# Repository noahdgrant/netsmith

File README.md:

<h1 align="center">
  <picture>
    <source media="(prefers-color-scheme: dark)" srcset="docs/assets/logo-dark.svg">
    
  </picture>
</h1>

A language and tools for designing electronics as code: schematics, solvers, checks and PCB fabrication outputs.
A board is a set of parts and the nets that join their pins,
written as text. netsmith checks it, picks real parts that work in the worst case, and
exports files for CAD tools and for a board house. It writes a KiCad 9 schematic, and a placed
and routed PCB with a Gerber package for JLCPCB, on two layers or on four with ground and
supply planes inside. The editor (`netsmith view editor`) shows the source and the board in a
browser.

Status: early (v0.1). The examples in `examples/` build and pass KiCad's checks where KiCad is installed, except `carrier_and_cards.nsm`, whose invented parts have no KiCad symbol (it is checked and solved only). The rest build and fab with no KiCad at all (see Install). Some of the decisions behind the language are still `proposed` and wait for review (see Limitations).

## An example

`examples/led.nsm` is a board with a 5 V supply, a resistor and an LED. The `~>` line is the
series circuit, and it carries its own equation: the supply's voltage less the LED's forward
voltage, over the resistance, is the LED's current. netsmith picks a resistor and an LED from a
catalog so that the current stays in the LED's window in the worst case, for every tolerance.

```nsm
board LedExample {
    .process: TwoLayer {
        .stackup.thickness &= 1.6mm
    }

    .supply: Rail {
        .voltage &= 5V +/- 5%
        .pos.net &= "VCC"
    }
    .led: Led {
        .current &= 5mA..15mA
    }
    .r1: Resistor {}

    .power_in: Header1x2
    .supply.pos ~ .power_in.p1
    .supply.neg ~ .power_in.p2

    .supply.pos ~> .r1 ~> .led ~> .supply.neg
}
```

The imports and doc comments are left out here; the complete file is `examples/led.nsm`.

## Install

- Build from a checkout: `cargo install --path crates/netsmith-cli --locked` (the package is
  `netsmith-cli`; the program it installs is `netsmith`). It needs Rust; with Node 20 or newer
  it also builds the editor's page (without Node the editor shows a page that says it was not
  built, ADR 0114).
- Or straight from GitHub, with no checkout:
  `cargo install --git https://github.com/noahdgrant/netsmith netsmith-cli --locked`.
- Or take the `netsmith-<version>-<target>.tar.gz` archive (`.zip` on Windows) from the
  [releases](https://github.com/noahdgrant/netsmith/releases), check it against its `.sha256`
  file and put the binary on your `PATH`. The release workflow builds them for Linux, macOS and
  Windows (`scripts/release-build.sh` makes one) and attaches them to a release when its tag is
  pushed. v0.1.0 and v0.3.0 have none (their builds failed; 0.3.1 is the first of the 0.3 line
  with archives): the release pull request now runs the same build before it is merged.
- netsmith is not on crates.io yet.

### KiCad is optional

netsmith needs no KiCad to write, check, solve, see, build or fab a board, and it needs no
KiCad library or `kicad-cli` for any of them (ADR 0097). It draws the ICs and the linear
regulator from the part's pin table, as a plain box, and the resistors, capacitors, inductors,
LEDs, diodes, FETs, fuses, crystals, switches, ferrite beads, headers and sockets, USB-C and
coaxial connectors, test points, mounting holes, fiducials and the power flag as conventional
glyphs, with the pins where KiCad's symbols have them. Every footprint of the standard
library is generated or written from the maker's drawing (`std/libs/`). The `.kicad_sch` and
`.kicad_pcb` files it writes are KiCad's formats, and KiCad opens them. CI proves it: the
`no-kicad` job builds and fabs the examples on a runner with no KiCad, with the libraries and
`kicad-cli` hidden (`scripts/check-no-kicad.sh`), and fails if a run says KiCad is missing. No
example names a part of KiCad's own, so every one of them builds and fabs.

KiCad 9 is needed for these, and for nothing else:

- The ERC and DRC cross-check: `kicad-cli`, and in the editor the PCB findings that run
  KiCad's check (without it the findings list says "KiCad not found: set KICAD_CLI or install
  KiCad", once). `board fab --cross-check` plots the board with KiCad as well (with no KiCad it compares the
  Gerbers with the board with netsmith's own viewer alone), and `fab` runs netsmith's own design
  rules check without it.
- A project whose own `kicad.toml` names a KiCad symbol or footprint that netsmith does not
  make, with no `[[library]]` of the project and no `gen:` footprint for it. Only then does a
  run stop, and the message names the part, the id and the line of `kicad.toml`, lists where
  netsmith looked, and gives the three ways out: install KiCad 9, supply the file through a
  `[[library]]`, or use a `gen:` footprint (or omit `symbol`, to have the symbol drawn from the
  pin table).

netsmith finds KiCad's `symbols` and `footprints` folders by itself, and `kicad-cli` as
`$KICAD_CLI`, else `kicad-cli` or `kicad-cli.exe` on `PATH`, else (under WSL only) the newest Windows KiCad in
`/mnt/c/Program Files/KiCad/<version>/bin`; set `NETSMITH_KICAD_SYMBOLS` and
`NETSMITH_KICAD_FOOTPRINTS` to name the folders. `NETSMITH_NO_KICAD=1` makes every one of those
searches find nothing, whatever is installed (for tests and CI). KiCad 9 is the version
tested: Windows KiCad 9 under WSL on a real install, KiCad 9 on Linux in the CI `kicad` job,
and, in the release workflow, the starter board's `init`, `build` and `fab` with KiCad 10 on
macOS and Windows runners (#6). The folders of KiCad 8 are looked for too, and nobody has
tried them.

## Use it

```sh
mkdir blink && cd blink
netsmith project init       # netsmith.toml, src/main.nsm (a working LED board), agent files (`project refresh` updates them after an upgrade)
netsmith board build      # a KiCad schematic in out/
netsmith view editor     # the source and the board in a browser, at 127.0.0.1:8787 (`--offline` asks no supplier for stock or price, and the bill of materials says they are not checked; `board fab --offline` says it in `fab-notes.txt`)
netsmith board fab        # a package for JLCPCB in fab/: Gerbers, drill, bom.csv, cpl.csv, fab-notes.txt, the board's 3D scene as `<board>.glb` (`--no-glb` or `glb = false` in netsmith.toml leaves it out), the board as STEP for mechanical CAD as `<board>.step` (`--no-step` or `step = false` leaves it out), the schematic as `<board>-schematic.pdf`, a page for each sheet (`--no-pdf` or `pdf = false` leaves it out), and for a board with pin requests its pin map for firmware from the final layout (`.pins.h`, `.pins.json`)
netsmith dev board3d --format json   # the board's 3D facts for an agent: heights, limits, overlaps (docs/BOARD3D.md)
netsmith dev board3d --glb board.glb   # the same scene as glTF 2.0 binary, the file the editor's 3D view shows
netsmith view 3d --view iso --picture board.png   # the board drawn in 3D to a PNG by netsmith's own rasterizer, no GPU or KiCad (docs/BOARD3D.md)
netsmith view schematic --format pdf   # the schematic the editor draws as a PDF, a page for each sheet (`--format svg` or `png` for a picture, `--sheet NAME` for one sheet), no KiCad or browser
netsmith view editor-3d --view top --highlight J1 --picture j1.png   # drive the 3D view of the running editor with render's flags, and save its picture (docs/BOARD3D.md)
netsmith layout show   # where each part is in the layout file; `layout set PATH --at X,Y --turn 90 --side bottom --lock` writes one entry, `layout check` finds a wrong path or turn, `layout summary` sums up a placement (wire, decoupling, modules, area and free space per face, nets, the parts near a part, the distance between two pads; the editor's PCB view has it as the Summary tab) `layout compare` says what moved between two layout files, `layout regenerate PATH` places one module again with the rest held, `layout capture` writes the placement and its seed as the layout file, an entry for every part, to freeze a result, `layout fit PATH` says where one part fits with the rest where they are (`--as-laid-out` asks of the layout file's board with nothing placed), `layout parts [PATH...]` gives each part's frame, courtyard shapes and pads (net, place, size) as data, with the placement's findings beside them, and `layout export --out FILE.kicad_pcb` writes the placed board, not routed, for KiCad (also with findings), whose moved parts `layout import FILE.kicad_pcb` brings back (the editor's PCB view has the same files as its "Download KiCad board" button; language guide, "The layout file")
netsmith board compare a.kicad_sch b.nsm   # are two designs the same circuit?
netsmith mcp   # the commands as tools for an agent host over the Model Context Protocol; `claude mcp add netsmith -- netsmith mcp`, `--project DIR` for a host that cannot start it in the project's folder, `--editor [PORT]` to act on the page of a running editor; a short tool list, the whole help of a command a resource (language guide, "The MCP server")
netsmith board compare --ref main          # what changed in the circuit since the branch `main`
```

Without a project, `netsmith board build examples/led.nsm --out out` works on one file. `netsmith
--help` and `netsmith <command> --help` document every command and flag, and `docs/LANGUAGE.md` ("Projects and netsmith.toml")
describes the project folder.

The first `build` or `fab` also writes `src/main.lock.toml` beside each source file: the catalog
row each part was picked as. Commit it, as you commit `Cargo.lock`. Later runs hold each part
to its row, and `--locked` makes a run that would change the picks an error (`docs/LANGUAGE.md`,
"The pick lock"). `netsmith project lock --update` refreshes the lock after a catalog edit and prints
what changed (`--part r1,u2` or `--except r1` takes new picks for some parts only), and
`netsmith project lock --check` fails when it is not current, for CI. `lock = "top_level"` or `"none"` under
`[project]` in `netsmith.toml` keeps unit-test and scratch sources free of lock files.

The boards in `examples/` carry their locks, committed beside the sources, and CI runs
`netsmith project lock --check` over every one of them (`scripts/check-example-locks.sh`, the `locks` job). A
change to a catalog, `std/` or the solver that would move a pick of an example fails the job until
someone runs `netsmith project lock --update` in the example and the diff of the lock is reviewed. Each
example also commits its design, `<stem>.design.json` (`netsmith board build --emit-design`), which the
`designs` job checks the same way (`scripts/check-example-designs.sh`, whose `--update` rewrites it).
`NETSMITH_TIMINGS=1` prints how long each stage took.

The editor also opens in a window of its own: the desktop shell in `desktop/` (a separate Cargo
workspace, built with Tauri, on Linux for now) starts `netsmith view editor` in the project folder it is
opened with (`netsmith-desktop [FOLDER]`, the current folder by default) on a free port, shows it,
and stops it when the window closes. It needs WebKitGTK (`libwebkit2gtk-4.1-dev`) to build:
`cargo build --manifest-path desktop/Cargo.toml --features window`. It starts the `netsmith` that
`NETSMITH_BIN` names, else the one beside it, else the one on `PATH`. No release ships it yet.

**Read `fab-notes.txt` before you order.** It lists what netsmith could not verify, for
example the pick-and-place rotation of a package that no board of yours has been assembled
with, the parts you solder yourself (`hand-solder:`), the parts you ship to the board house
(`consigned:`, ADR 0084) and, for each supply channel, the numbers to buy those by (`buy from`,
ADR 0143). Check JLCPCB's order preview for those.

## Where to read next

- `docs/LANGUAGE.md`: the language guide's index; its chapters are in `docs/language/`, with a quick
  start, every construct with a tested example and the real error you get when you misuse it, and the
  standard library.
- `docs/PIPELINE.md`: the stages a design goes through, from source to a fab package, with diagrams.
- `docs/BOARD3D.md`: `netsmith dev board3d`, the board's 3D scene as a JSON report and as a `.glb` file, and `netsmith view 3d`, the same scene as a PNG, and `netsmith view editor-3d`, which drives the 3D view of a running editor.
- `docs/CONCEPTS.md`: how parts, modules, boards and systems combine.
  `docs/PROJECT-LAYOUT.md`: a repository with several boards.
- `docs/MIGRATING.md`: what to change in a project that a newer netsmith refuses, release by release, with the old and the new spelling.
- `docs/RELEASING.md`: the order of a release, with the `kicad-cli` stress run (`scripts/stress-kicad.sh`).
- `docs/symbol-gallery.html` (open it in a browser): every symbol netsmith draws, beside the KiCad
  symbol it replaces. `cargo run -p netsmith-tools --example symbol_gallery -- --out docs --file
  symbol-gallery.html` writes it again.
- `GLOSSARY.md`: the vocabulary (an index of `docs/glossary/`). `docs/DESIGN-RULES.md`: the rules the language follows.
  `docs/adr/`: the decisions behind the design.
- Contributors and agents: `AGENTS.md`. Open work is in the
  [GitHub issues](https://github.com/noahdgrant/netsmith/issues).

## Limitations

netsmith analyzes a worst-case DC operating point of the picked parts: every voltage, current and power is checked over the ranges the design states (ADR 0076). It does not model time. Startup, inrush, ripple, filter response, AC and heating are not analyzed (a part's power rating is checked; its temperature is not computed). Closed-form checks for some of these, such as an RC time constant or a buck's output ripple, are the next step and are laid out as options in `docs/research/closed-form-checks.md`. Running a circuit simulator on demand is a later option, issue #306.

- Price and stock are unknown until a supply provider is asked, and no provider asks a
  supplier yet (#8, #30). Catalogs hold only verified parts (#66). A generic part (a value
  no catalog row has) exists for resistors, ceramic capacitors, inductors and LEDs; a generic
  capacitor has no bias curve and resolves only to a row that has one (ADR 0047, #31).
- netsmith writes its own Gerbers, drill and placement files, and JLCPCB has not yet taken
  them (#12, #61).
- A board outline is a rectangle with equal rounded corners or a `polygon` of corners, fillets
  and arcs, and a cutout is a rounded rectangle, a slot or a circle (#57). A panel repeats
  one board on a V-cut grid (#62).
- The placer and router can leave a tight board unrouted (#3, #58).
- Physical intent (the outline, cutouts, holes, keepouts and where parts must be) is in a file of
  its own beside a board, `<stem>.physical.nsm`, and the same lines in the board are an error
  (ADR 0048, #52). The board level is built, and the placer and `fab` hold a relation between
  two parts (ADR 0045), and the editor writes the keepouts it draws to that file. A module owns a
  physical file of its own, which it names, and a board's file may only narrow it (#813); a
  physical file for a `system` or a `panel` is not built. The readings are in the ADR's "Built".
- Nine ADRs in `docs/adr/` are `proposed` and wait for review: 0049, 0050, 0051, 0072, 0098, 0099, 0100, 0102 and 0103.

## Licence

netsmith is MIT licensed (`LICENSE`).

netsmith keeps no copy of KiCad's symbols or footprints. The symbol of an IC is drawn by
netsmith from the part's pin table (a plain box and pins, ADR 0097), and those of the passives,
discrete parts, connectors and mechanical parts from the electrical and mechanical conventions
(IEC 60617, IEEE 315), not from KiCad's files. Only for a symbol or footprint that a project's
own `kicad.toml` takes from KiCad and that netsmith does not make does it read the ones
installed with KiCad (CC-BY-SA 4.0 with a design exception) at run time. `board build --portable` and
`board fab --portable` copy the library entries a board uses, and their 3D models, into the board's
folder so that it opens in KiCad anywhere; those copies are KiCad's files under CC-BY-SA 4.0, the
folder says so in `LICENSES.md`, and the design in it stays free of the licence by the
exception. The tests that need no KiCad write small libraries of their own (the dev-only crate `netsmith-testkit`). For a package or a part that KiCad's libraries lack,
`std/libs/` holds a small symbol and footprint library of netsmith's own, written by netsmith
from a manufacturer's package drawing (MIT, like the rest; ADR 0087). The footprints it makes are original code that computes
IPC-7351B land patterns from published package dimensions (ADR 0043); the test that checks
them reads KiCad's footprints and bundles none. The formulas and tables were learned from the
`kicad-footprint-generator` repository (GPL-3.0-or-later; no code was copied) and the package
dimensions of the QFN rows are numbers from its data files and the datasheets they cite.

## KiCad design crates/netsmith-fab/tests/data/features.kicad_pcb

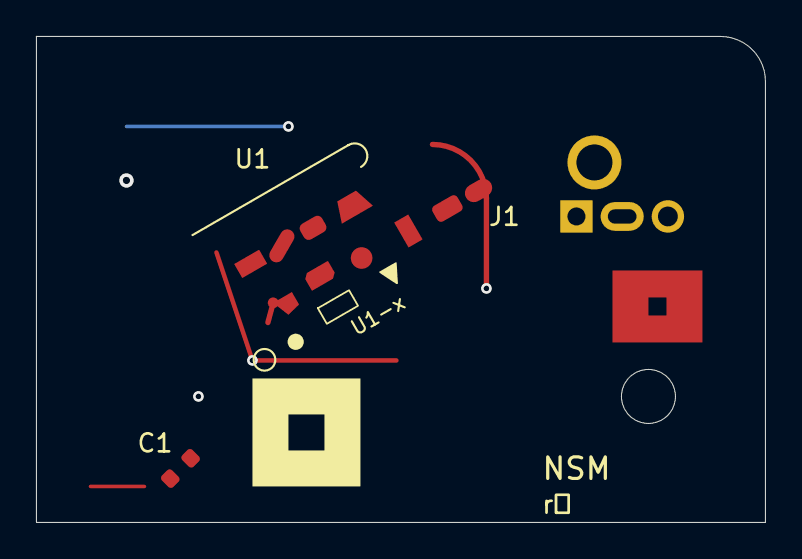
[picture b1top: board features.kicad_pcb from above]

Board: 4 copper layers, 40.5 x 27.0 mm, 4 parts (1 on the bottom side), 3 nets.

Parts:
C1: 100n; C_0603
J1: hdr; Header
R2: 1k; R_0603
U1: shapes; Shapes

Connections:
GND: C1.2, J1.1, R2.1, U1.1, U1.5
SIG: J1.3, R2.2, U1.3, U1.7, U1.8, U1.9, U1.10
VCC: C1.1, J1.2, U1.2, U1.6

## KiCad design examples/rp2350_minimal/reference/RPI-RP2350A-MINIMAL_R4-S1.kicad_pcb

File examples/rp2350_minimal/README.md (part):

# RP2350A Minimal

A port of Raspberry Pi's open **RP2350A Minimal** reference board to netsmith, as a showcase.
**The schematic is done** (`src/main.nsm`, the board `Rp2350Minimal`): the same circuit as
theirs, proved net by net by a test. **The physical file is done** (`src/main.physical.nsm`: the
outline, the four mounting holes, the places of the connectors and buttons), and `netsmith board fab`
writes a PCB that the parity checker finds equal to Raspberry Pi's in every way that must match
(see Parity and The result). Its parts are drawn with Raspberry Pi's footprints (#728, see
Parts), so the placer arranges them otherwise than before, and which seed the router finishes
moved with it: seeds 0 and 4 route completely (about 3 to 4 minutes in a debug build on a busy
machine), seeds 1, 2 and 3 leave three, two and one connection after the router's 300 s (#731).
The design rules check measures the ring of each of the nine vias in the RP2350's exposed pad
with the exposed pad round it, as KiCad does, and finds none too thin (see The reproduction). The
figures of The result are from before.

## Source

- The design: <https://pip.raspberrypi.com/documents/RP-010328-CA>, a zip of the KiCad 10
  schematic, board, project, a PDF and a bill of materials.
- Name and revision: `RPI-RP2350A-MINIMAL_R4-S1`. The board file is revision R4 and the
  schematic is revision S1; both title blocks are dated 2026-07-03 ("RP2350A QFN-60 Minimal
  Design Example"). One schematic sheet, 43 parts, two copper layers.
- Licence: MIT, Copyright (c) 2026 Raspberry Pi Ltd. The notice is in `LICENSE`, as they ship
  it, and stays with every copy of anything in this folder that comes from their design
  (`reference/`).

**The circuit is Raspberry Pi's. The port, the netsmith source and the tools in this folder
are netsmith's** (MIT, like the rest of the repository).

## Goal

1. **The same nets.** The schematic of the port and Raspberry Pi's design are the same
   circuit: the test `every_pad_has_the_same_pads_on_its_net_as_in_raspberry_pis_board` proves
   it by comparing the wiring alone (see "Same nets"). The bare `netsmith board compare` of the two
   files answers `different`, because it pairs parts by footprint name (see "Run it").
2. **A matching PCB where it matters.** A board made by `netsmith board fab` is interchangeable
   with theirs in these ways, and a checker with tolerances will fail when one is off:
   - the board outline and the four mounting holes;
   - the connectors (J1 to J4), the buttons (SW1, SW2) and the pin headers: the same
     positions, rotations and pads, with each header pin carrying the same signal.

   The other parts (MCU, flash, crystal, regulator, inductor, decoupling) may be anywhere,
   and the routing will differ; the checker reports them and does not fail on them.

## What is here

- `netsmith.toml`, `src/main.nsm`, `src/oscillator.nsm`, `src/main.lock.toml`: the project, its
  board and the crystal's module (see The board). The lock is the catalog row each part was
  picked as; commit it, refresh it with `netsmith project lock --update`.
- `catalogs/capacitor.csv`, `catalogs/resistor.csv`: two rows the standard catalogs lack, the
  10 uF 0805 capacitor and the 0 ohm link (see The catalog rows).
- `src/tactile_switch.nsm`, `catalogs/ldo.csv`, `catalogs/inductor.csv`,
  `catalogs/tactile_switch.csv`, `kicad.toml`, `libs/rp2350_original.pretty/`: the regulator U2,
  the inductor L1 and the buttons SW1 and SW2 (see Parts).

- `src/rp2350a.nsm`, `catalogs/rp2350a.csv`, `kicad.toml`: the MCU, U1 (see Parts).
- `src/flash.nsm`, `src/crystal.nsm`, `catalogs/w25q128jv.csv`, `catalogs/abm8_272_t3.csv`,
  `kicad.toml`: the QSPI flash, U3, and the crystal, X1 (see Parts).

- `src/amphenol_10103594.nsm`, `src/jst_sm03b_srss_tb.nsm`, `src/samtec_tsw_118.nsm`,
  `catalogs/micro_usb.csv`, `catalogs/jst_srss.csv`, `catalogs/samtec_tsw_118.csv`,
  `libs/rp2350_original.pretty/`: the
  connectors J1 to J4 (see Parts). The footprints are Raspberry Pi's, files of the project's own library, and
  need no KiCad.
- `LICENSE`: Raspberry Pi's licence text.
- `reference/RPI-RP2350A-MINIMAL_R4-S1.kicad_pcb`: their board file, unchanged (1.6 MB).
- `reference/placements.toml`: the facts the checker needs, read from that file: the outline,
  the mounting holes and, for every footprint, its place, rotation and pads. The header of the
  file says what the origin and axes are, and which entries must match (`must_match = true`).
  Regenerate it with
  `cargo run -p netsmith-tools --example reference_table -- reference/RPI-RP2350A-MINIMAL_R4-S1.kicad_pcb > reference/placements.toml`
  (run from this folder); a test checks that the file is what the program prints.
- `reference/parts.toml`: the parts file of the port, Raspberry Pi's designator of each part by its
  member path (see Parity): all 43, the four mounting holes `hole1` to `hole4` as MH1 to MH4. The
  nets proof and the parity check read it.
- `src/main.physical.nsm`: the board's physical file: the outline, the mounting holes and the
  places of J1 to J4, SW1 and SW2, each number read from their board (see The physical file).
- `src/main.pcb.toml`: the layout file, with only a placer seed (see The physical file).
- `case/base.step`, `case/lid.step`, `case/make_case.py`, `case/LICENSE`: a case of our own
  (MIT), which the physical file names, and the script that writes it (see The case).
- `libs/rp2350_original.pretty/none_mh_npth_fd2p75mm_sm3p15mm_ko6mm.kicad_mod` and its row in `kicad.toml`:
  the 2.75 mm non-plated hole with the 3.15 mm mask opening of Raspberry Pi's (the standard rows
  have only M2 and M3; the parity checker compares the pad's size).
- `reference/parity-overlay.svg`: the picture of the parity check (see Parity).

## Parts

**Every footprint is Raspberry Pi's own** (#728): the files of `libs/rp2350_original.pretty`
are the footprints of their board, written out by `cargo run -p netsmith-tools --example
footprint_from_board -- reference/RPI-RP2350A-MINIMAL_R4-S1.kicad_pcb <REF>
libs/rp2350_original.pretty` with what the board adds taken off (place, identifiers, nets, 3D
models). The rows of `kicad.toml` name them: a `[[part]]` row for each part of the project's
own, and a `[[member]]` row for each part of a standard row (the capacitors, the resistors and
the regulator), since a project may not map a kind and package that `std/kicad.toml` maps and
their board draws two of the 0402 capacitors (C6, C7) on a wider land than the others. So the
pads, the courtyards (which are the parts' bodies in their library: the pads stick out of them)
and each footprint's frame are theirs, and the reproduction places every part as their board
does. One change: their SOT-223 numbers the tab 4, and the copy numbers it 2, as the standard
regulator's pin table does (U2 below). Where a bullet below says what a maker's document draws,
it records what the project's earlier footprints were drawn from and how it compares with
Raspberry Pi's pads.

- **U1, `Rp2350A`** (`src/rp2350a.nsm`): Raspberry Pi's RP2350A in the QFN-60, 7 x 7 mm,
  0.4 mm pitch package: a pin table of 60 pads and the exposed pad (pad 61, the ground).
  Source: the RP2350 datasheet (document RP-008373-DS; the PDF's colophon says Release 8, build
  date 2026-10-01), Figure 2 (printed page 15) and Tables 1673 to 1679 (pages 1331 to 1335).
  The table is written by hand: the datasheet is CC BY-ND and the owner's rule is no copied
  tables, so only the facts (numbers, names, kinds) are taken. The datasheet's Table 1679 lists
  the IOVDD pads without pad 1 and with pad 54, which is QSPI_IOVDD; the figure and Raspberry
  Pi's board have IOVDD on pad 1, and the part follows them.
- **Footprint** (`kicad.toml`): Raspberry Pi's `rpi_rp2350a_vias`: lead pads 0.70 x 0.23 mm,
  the 3.4 x 3.4 mm exposed pad and nine plated vias in it, all pad 61. Its body, pitch and
  exposed pad are those of the package drawing (page 1324); the recommended footprint (page
  1325) draws 7.75 mm over the pads. The generator's `QFN-60-1EP_7x7mm_P0.4mm_EP3.4x3.4mm`,
  which the project used before, has 0.80 x 0.20 mm leads. The symbol is drawn from the pin
  table.
- **Catalog row** (`catalogs/rp2350a.csv`): JLCPCB C42411118, Extended, with the page it was
  read from and the day. Price and stock are not recorded.
- **U3, `W25Q128Jv`** (`src/flash.nsm`): Winbond's W25Q128JVSIQ, a 16 MB (128 Mbit) QSPI NOR
  flash in the 8-pin SOIC 208-mil package. The pin table is written by hand from Winbond's
  datasheet "W25Q128JV, 3V 128M-bit serial flash memory with dual/quad SPI", Publication Release
  Date August 23, 2021, Revision I (79 pages), fetched on 2026-11-10 from
  <https://www.winbond.com/resource-files/W25Q128JV%20RevI%2008232021%20Plus.pdf>: Figure 1a and
  section 3.3 "Pin Description SOIC 208-mil, WSON 6x5-mm / 8x6-mm" (printed page 5) for the
  pads, names and I/O, and section 10.1 "8-Pin SOIC 208-mil (Package Code S)" (printed page 67)
  for the package. The datasheet writes `/CS`, `/WP` and `/HOLD`; the table writes `CS#`, `WP#(IO2)`
  and `HOLD#/RESET#(IO3)`, the same signals. Levels, ratings and timing are left out, so the
  part is a boundary of the design.
- **U3 footprint** (`kicad.toml`): Raspberry Pi's `generic_soic127p790x195-8`, pads 1.7 x
  0.65 mm at x = +-3.6 mm, 1.27 mm apart. The datasheet draws no recommended land pattern; the
  generator `SO` with the datasheet's numbers (pitch 1.27 mm, body 5.3 x 5.3 mm, 7.7 to 8.1 mm
  over the leads, lead width 0.35 to 0.48 mm, lead length 0.50 to 0.80 mm), which the project
  used before, puts 1.6 x 0.6 mm pads at the same centres.
- **X1, `Abm8272T3`** (`src/crystal.nsm`): Abracon's ABM8-272-T3, 12 MHz, a 3.2 x 2.5 x 0.8 mm
  ceramic crystal with four pads: the crystal on pads 1 and 3, ground on 2 and 4. The standard
  `Crystal` has two terminals, so the project has its own part (all four pins `passive`; the pin
  names are ours, the drawing numbers its pads). Source: Abracon's "Source Control Drawing"
  ABM8-272-T3 (drawing # 456603, Revision B, date of issue September 16th, 2024; a PDF of three
  pages, numbered 2, 4 and 6 of 9), fetched on 2026-11-10 from
  <https://abracon.com/datasheets/ABM8-272-T3.pdf>: "Key Electrical Specifications" (page 2)
  and "Mechanical Dimensions" (page 4). Frequency 12 MHz, tolerance +/- 30 ppm at 25 C and
  stability +/- 30 ppm over -40 to +85 C (the catalog row has them added, +/- 60 ppm, as the
  standard crystal catalog does; aging, +/- 5 ppm in the first year, is not included), load
  capacitance 10 pF, equivalent series resistance 50 ohm at most.
- **X1 footprint** (`kicad.toml`): Raspberry Pi's `generic_xtalcc320x250x80-4`, with pads
  1.4 x 1.2 mm at +-1.1 mm and +-0.85 mm, as the generator's
  `Crystal:Crystal_SMD_3225-4Pin_3.2x2.5mm` that the project used before has them (its
  courtyard is larger than their body-sized one). The drawing's
  terminals (0.9 x 0.8 mm, page 4) lie inside them; the extract of the datasheet that was
  read has no recommended land pattern. The pad numbers are the drawing's.
- **Catalog rows** (`catalogs/w25q128jv.csv`, `catalogs/abm8_272_t3.csv`): JLCPCB C97521
  (Basic) and C20625731 (Extended), each with the page of the JLCPCB parts library it was read
  from and the day, 2026-11-10. Price and stock are not recorded.
- **What the reference says about them** (checked by the tests against
  `reference/placements.toml`): U3's pads carry `QSPI_SD0` to `QSPI_SD3` on the pins the
  datasheet calls IO0 to IO3 (pad 5 DI, 2 DO, 3 WP#, 7 HOLD#/RESET#), `QSPI_SCLK` on CLK, `GND`
  and `+3V3`. The one name that differs is pad 1, CS#: it is on `FLASH_SS`, which reaches the
  MCU's `QSPI_SS` through a resistor (R10), has a pull-up to `+3V3` (R1) and a resistor to `GPIO0`
  (R9) on Raspberry Pi's board, so that net is not named like the pin. X1's pads 2 and 4 are `GND`,
  pad 1 is `XIN` and pad 3 is on the net of a damping resistor (R2) to `XOUT`.
- **Left out on purpose:** the alternate functions of the pins (a GPIO has `GPIO`, and
  GPIO26 to GPIO29 also `ADC0` to `ADC3`; the board chooses `GPIO` on those four) and every
  level, rating and model. The QSPI pins have their one function each, and `QSPI` is a `Qspi`
  master (`std::bus`) that the board joins to the flash's `Qspi` with one `~` (ADR 0129); the
  select goes through R10, so the board joins it by hand. With no model the
  part is a boundary of the design, and the checks that need a number are listed as not
  evaluated.

### The connectors, J1 to J4

Since #728 the four are drawn with Raspberry Pi's own footprints (`libs/rp2350_original.pretty`,
see Parts), whose pads are the ones described below and whose courtyards are theirs. What
follows is how the project's earlier footprints were written from the makers' drawings, which
agreed with Raspberry Pi's pads. Their pads must equal Raspberry Pi's, so the footprints were
written pad for pad against the board's table (`reference/placements.toml`); a test compares number, centre (0.01 mm), size
(0.05 mm), drill (0.01 mm), shape and kind for each of the four, and a fixture board builds with
the parts and no KiCad install. The parts only say what a connector is; which signal is on
which pin, and where each stands, is the board's. Origin and axes are those of Raspberry Pi's
footprints (x right, y down, the part seen from the component side), the same as the drawings'
datum where they have one. Numbers are mm. **No dimension was guessed**; what is not on a drawing
is listed as assumed, and where the board differs from a drawing the footprint follows the board
and says so.

- **J1, `Amphenol10103594`** (`src/amphenol_10103594.nsm`): Amphenol FCI 10103594-0001LF, micro-USB
  B receptacle, LCSC C428495, JLCPCB Extended (the page was read on 2026-11-10;
  `catalogs/micro_usb.csv`; price and stock not recorded). Pins: VBUS 1, D- 2, D+ 3, ID 4, GND 5
  and the shield, one pin of the six pads 6 to 11. `provides Connector`.
  Footprint `USB_Micro-B_Amphenol_10103594-0001LF`, 15 pads (11 numbers: the five contacts, and
  six shell numbers of which 6, 7, 9 and 10 each have a surface pad and a plated slot).
  - Source: Amphenol FCI drawing 10103594 ("MICRO-USB B-TYPE RECEP."), revision A, ECN
    T10-0002, dated 1/7/10, printed 2010-06-02 (the PDF that LCSC links for C428495,
    `datasheet.lcsc.com/datasheet/pdf/ca5a42dbf95ebfb4fb84a094027e7ce9.pdf`, one sheet, SHA-256
    `e119d95457dc`), the view "RECOMMENDED PCB Pattern" (tolerance +/-0.05). The drawing carries
    "Tous droits strictement reserves ... All rights strictly reserved. Reproduction or issue to
    third parties in any form whatever is not permitted without written authority from the
    proprietor" in its margin. Nothing was copied: only the dimensions were taken, and the
    owner accepted that reading for Amphenol's SMA drawing on 2026-11-10; it has **not** been said
    of this one, so it needs the owner's word.
  - **Read** (labels, 500 to 900 dpi): signal pads 0.40 wide, 0.65 pitch (0.65, 0.40), 1.75 long,
    their top 3.70 above the datum line (3.70, 1.75); the datum line passes through the centres of
    the two lower slots (3.03 below the upper slots' centres); upper shell pads 2.00 wide
    (2.00), 0.73 above and 0.73 below the slot centre (0.73 and 2.30), with a slot 0.65 x 1.05 at
    +/-2.425 (4.85, 0.65, 1.05); the T-shaped land from y = -2.05 to -1.35 for its bar (2.05,
    1.35), 7.80 over the bars' outer edges (7.80), 6.75 over the stems' (6.75), 4.15 between the
    stems' inner edges (4.15), stems ending 0.60 short of the PCB end 1.70 below the datum (0.60,
    1.70) with R0.40 corners; lower slots 0.70 x 1.20 with 6.15 between their outer edges (6.15,
    4.75, 0.70, 1.20); the middle pads 0.50 apart and 3.35 over all (0.50, 3.35), from 1.00
    above the datum to 1.50 below it (1.00, 1.50).
  - **Derived by arithmetic:** the shell pads' centre x (+/-2.9, from 7.80 and 2.00) and height
    1.46 (0.73 twice; Raspberry Pi's is 1.45); the slot centres (+/-2.725, from 6.15 and 0.70;
    +/-2.425 from 4.85); the T-land's stem (x from -3.375 to -2.075, bottom at 1.70 - 0.60 =
    1.10), as the polygon of pads 7 and 10 (the same outline as Raspberry Pi's custom pads); the
    contacts' centre y, -2.825.
  - **Differs from the drawing, the footprint follows Raspberry Pi's board:** the two middle
    pads (8 and 11) are 2.10 long and centred at y = 0.05 in Raspberry Pi's board (from -1.00 to
    1.10); the drawing has them 2.50 long, to 1.50. Their centres are x = +/-0.95 there against
    +/-0.9625 from the drawing's 0.50 gap and 3.35 span (0.0125 apart; the width, 1.425, is the
    same). The drawing is revision A of 2010; whether Amphenol drew another revision, or
    Raspberry Pi shortened the pads, is not known.
  - **Assumed:** pad numbers 6 to 11 for the shell (the drawing numbers none: Raspberry Pi's);
    that the contact order VBUS, D-, D+, ID, GND is the USB micro-B's (Raspberry Pi's board
    puts those nets on pads 1 to 5; the USB-IF specification was not read); the plated ovals
    around the slots, 1.05 x 1.45 and 1.1 x 1.8 (Raspberry Pi's; the drawing hatches the lands
    and draws the slots only, a ring of 0.20 and 0.20 / 0.30 around them); copper on all layers
    and mask on the back only for them, as Raspberry Pi's; paste on the contacts only;
    the courtyard, the pads and 0.25 all round; the PCB end on `Dwgs.User`; no 3D model; the
    pick-and-place rotation is unverified.
- **J4, `JstSm03bSrssTb`** (`src/jst_sm03b_srss_tb.nsm`): JST SM03B-SRSS-TB(LF)(SN), 3 contacts,
  1.0 mm pitch, side entry, two mounting tabs, LCSC C160403, JLCPCB Extended (read 2026-11-10;
  `catalogs/jst_srss.csv`). Pins 1, 2, 3 and `MOUNT` (pads 4 and 5). `provides Connector`.
  Footprint `JST_SM03B-SRSS-TB_1x03-2MP_P1.00mm_Horizontal`, 5 pads.
  - Source: JST, "SR/SZ CONNECTOR, 1.0mm pitch" (the PDF that LCSC links for C160403,
    `datasheet.lcsc.com/datasheet/pdf/e03a82bcc66e3c3589917313e54d45e2.pdf`, 3 pages, SHA-256
    `8f01930d3601`; no revision or date is printed): page 1, "PC board layout ... <SMT type>,
    Side entry type" ("Dimensions above should serve as a guideline", tolerances non-cumulative);
    page 3, "Shrouded header (SMT type)" for the part number and the 3-circuit dimensions
    (A 2.0, B 5.0). No notice of copyright or confidentiality was seen.
  - **Read:** contact pads 0.6 wide at 1.0 pitch (0.6, 1.0); the tabs 1.2 wide and 1.8 long
    (1.2, 1.8) with their inner edges 0.7 beyond the outermost contacts' centres (0.7); 4.0 from
    the contacts' lower edge to the tabs' lower edge, 5.55 from the contacts' upper edge to it
    (4.0, 5.55); the tabs' lower edge 0.2 below the header outline's rear edge (0.2).
  - **Derived:** the contacts' length 1.55 (5.55 - 4.0); the tabs at x = +/-(1.0 + 0.7 + 0.6) =
    +/-2.3; with the origin at the rear edge of the header outline, the tabs' centres at y = -0.7
    (0.2 - 0.9) and the contacts' at -4.575 (0.2 - 5.55 + 0.775). They are Raspberry Pi's numbers
    to the last digit.
  - **Assumed:** the origin and the numbering (contacts 1 to 3 from the left, the tabs 4 and 5;
    the drawing numbers neither; Raspberry Pi's board does so); paste on all pads; courtyard,
    the pads and 0.25; no body, silkscreen or model; the rotation unverified.
- **J2 and J3, `SamtecTsw11807LD`** (`src/samtec_tsw_118.nsm`): Samtec TSW-118-07-L-D, 2 x 18 pin
  header, 2.54 mm pitch, through hole; one part for both, 36 pins, `provides Connector`.
  Footprint `PinHeader_2x18_P2.54mm_Samtec_TSW-118-07-L-D`.
  - **Catalog row** (`catalogs/samtec_tsw_118.csv`): LCSC **C6887963**, the `lcsc_pn` that
    Raspberry Pi's board carries on J2 and J3 (`reference/RPI-RP2350A-MINIMAL_R4-S1.kicad_pcb`).
    Read on 2026-11-10 from LCSC's product page (`lcsc.com/product-detail/C6887963.html`): title
    TSW-118-07-L-D, manufacturer Samtec, 36 pins, 2 x 18, 2 rows, pitch and row spacing 2.54 mm,
    "Through Hole,P=2.54mm", so it **is the Samtec part**, not an equivalent. **Not read:** the
    JLCPCB parts page `jlcpcb.com/partdetail/C6887963` answered with its application shell only
    (no MPN, package or library type), so its LCSC offer has no `class` and the part is not in the `jlcpcb-assembly` channel (read its library from
    JLCPCB's page before ordering). Price and stock are not recorded.
  - **Assembly today:** the manifest says nothing, so the part is **soldered by hand** (ADR 0024:
    a through-hole part is `Hand` unless a board says otherwise, and a test holds it, with the
    LCSC number); the row does not change that. `AssemblyMode::Consigned` is the way to have
    JLCPCB place a header that is shipped to them.
  - **Not the generator's footprint:** `gen:PinHeader(rows=2, pins=18, pitch=2.54mm)` has pads of
    0.7 x the pitch, 1.778 mm, and its pins run down columns from the top left; Raspberry Pi's
    pads are 1.6 mm (the generator's are 0.178 mm larger, over the limit of 0.05 mm) and its pins
    run along the long axis, 1 in the row below, 2 above. A test shows the difference.
  - Source: Samtec, "Recommended P.C. Board Layout for (X)TSW Single, Double & Triple (Thru-hole
    & Right Angle)", revision A (`suddendocs.samtec.com/prints/tsw-xxx-xx-x-x-xx-xxx-footprint.pdf`,
    one sheet, SHA-256 `264658121ff2`); the product page
    <https://www.samtec.com/products/tsw-118-07-l-d> read on 2026-11-10 for the 36 pins and the
    pitch. The series print (47 pages) states a notice of confidentiality, and none of its numbers is used.
  - **Read:** holes 0.040 in (1.02 mm) diameter, 0.100 in (2.54 mm) apart, rows 0.100 in (2.54 mm)
    apart. The sheet states **no pad size**.
  - **Differs from the drawing, the footprint follows Raspberry Pi's board:** the drill is 1.00 mm
    (0.02 mm under Samtec's 1.02).
  - **Assumed:** the pads, 1.6 mm round, Raspberry Pi's (a ring of 0.30 mm; the drawing has none);
    pin 1 square; the numbering (pin 1 and the odd pins in the row at y = +1.27, the even pins at
    -1.27, pin 1 at the left end, as Raspberry Pi's); the origin at the middle of the 36 holes; a
    body outline of 2 x 18 pitches on `F.Fab`, the courtyard the pads and 0.25; no model.
  - **In 3D** (`docs/BOARD3D.md`): the footprint's name (`PinHeader_2x18_P2.54mm_...`) and its 36
    round plated holes on a full 2.54 mm grid make the 3D view draw it as a pin header: the
    `F.Fab` body as the plastic, to the generated family's 2.50 mm (F-226's body is .100 in,
    2.54 mm: the family's figure is used, 0.04 mm lower), and a 0.64 mm (.025 in, F-226's title)
    square post on each pad up to the catalog height, 8.38 mm. **The tails**: Samtec's catalog
    page F-226 (`suddendocs.samtec.com/catalog_english/tsw_th.pdf`, SHA-256 `3a5770b11668`, read
    2026-11-13), page 1, STRAIGHT PIN VERSIONS, lead style -07: B (2.54) .100, the tail under the
    body. Through the 1.6 mm board they stand 2.54 - 1.6 = 0.94 mm out of the bottom face, which
    `src/main.physical.nsm` states as `.pin_protrusion` for both headers (bought that length, not
    cut; the page prints no tolerance), so the 3D view, the `.glb` and the STEP file draw each pin
    through its hole and out, and the case fit measures them. `fab` then writes the `trim:` line
    every stated protrusion gets (`after soldering, cut the pins to protrude 0.94 mm from the
    bottom face, nothing lies over them`): they already do, so measuring one is the whole step.

## Parity

`netsmith dev parity <board.kicad_pcb> [--table <placements.toml>]
[--parts <parts.toml>] [--svg <overlay.svg>]`, run in this folder, compares the `.kicad_pcb` that `netsmith board fab`
writes (in `fab/<Board>/`) with Raspberry Pi's board, as `reference/placements.toml` states it.
It prints one line per item and `must-match: N ok, M failed`, writes the overlay (both boards at
one scale: Raspberry Pi's in blue, netsmith's in orange, a failing must-match item in red with
its offset) and exits 1 when a must-match item fails. The test
`rp2350_minimal_pcb_matches_raspberry_pi` runs `fab` and the checker in CI and fails when a
must-match item is not `ok`. The checking is `netsmith_tools::parity`;
`crates/netsmith-tools/tests/rp2350_parity.rs` tests it, also on Raspberry Pi's own board against
itself.

**The test does not wait for the router.** It runs `netsmith board fab --locked --route-timeout 20`
with no KiCad (`NETSMITH_NO_KICAD=1`), and takes the board file that `fab` writes complete or
marked INCOMPLETE (a run that the timeout stopped exits 1 and says `INCOMPLETE:`; any other
failure fails the test). The placer fixes every part before the router starts, so the checker
sees the same board whether the router finished or not, and the test takes about 25 s. It also
holds that `reference/parity-overlay.svg` is the overlay of that board.

**What is checked.** The report prints what each verdict compared, at its head. Must match (a
failure):

- the outline: the bounding box (width, height), the corner radius, the number of `Edge.Cuts`
  lines and arcs and each arc's radius (a corner cut by a line, or a cut-out inside the board,
  changes the count and fails though the box is the same);
- each hole's place and drill, whether it is plated, its pad's size and its pad's net (by name; a
  made-up name is no net);
- for the connectors, buttons and headers (J1 to J4, SW1, SW2), each part's position, rotation
  and layer;
- each pad, one by one: number, centre in its footprint, size and angle in the footprint's frame
  (a pad turned by 90 degrees has its width and height swapped, so the same copper written two
  ways is equal and a turned pad is not), shape, the box of a custom pad's polygon, drill (both
  sides of a slot, round against slot), type, copper layers (as sets: a pad on the other face
  fails), and net. The pads of one number (J1's shell has a
  surface pad and a plated slot for each of 6, 7, 9 and 10) are paired by the nearest centre in
  the footprint, and each pair is judged.

A part of nothing but non-plated pads is a mounting hole, and so is a plated `MountingHole*`
footprint of KiCad's library (its drilled pad is the hole; a ring of vias round it is not
compared); a connector with a peg is still a part and the peg is a pad of it. Reported, never a failure (`info`): the same figures of every other
part (MCU, flash, crystal, regulator, inductor, decoupling), pads reported as one line per part.
Not compared, because the table does not hold it: a rounded rectangle's corner ratio, a custom
pad's anchor shape and its polygon's shape inside the box, a pad's mask and paste layers, the
silkscreen, the courtyard and the routing. A table with no part, a part with no `must_match` or an
outline with no count of lines or arcs is an error, not a pass.

**The origin.** `fab` gives a board an origin of its own, so both boards are read from the
upper-left corner of the outline's bounding box (the smallest x and y of `Edge.Cuts`, KiCad's y
grows downward): it is a corner of the box in both files and needs no flip of an axis. A board
moved as a whole passes; the two corners as the files state them are an `info` line.

**The map.** Raspberry Pi's references and netsmith's differ, so the checker pairs them by the
member path: `reference/parts.toml` has a line `usb = "J1"` (the member path, then Raspberry Pi's
reference) for each part, and `fab` writes each footprint's member path on the board as a hidden
property (`netsmith_path`); a board with no such property is refused. A part of the table with no line is `unmapped`: a failure if it must match, else a
note. Map every part whose pads carry a net, U1 included: the nets are compared by name where
both names are plain (a leading `/` and the case are ignored; `Net-(...)` and `unconnected-...`
are not plain), and through the connectivity otherwise. A pad's net passes when the names are
equal, or when they differ and the same mapped pads are on the net in both boards (a warning
says so); two header pads on each other's nets fail. A name that differs, or of which one is
made up (`Net-(...)`, `unconnected-...` or none), with no other mapped pad on the net to vouch
for it fails: nothing vouches for it. A pad with no net is not a made-up name: where the pad's
net in one board has other pads (mapped or not) it does not pass against a pad that is on no net,
or alone on its own, in the other (both unconnected passes).

**Tolerances** (mm, degrees). The owner's: outline and mounting holes 0.05, positions of parts
0.1, rotation exact (modulo 360), pad numbers equal, nets equal. Chosen where the owner was
silent: the corner radius 0.05 and a hole's drill 0.05 (as the outline and the holes), a pad's
centre in its footprint 0.1 (as the positions), a pad's width, height and drill 0.05, the rotation
0.001 degree (the rounding of the file; a pad's angle in its footprint uses it too), a custom
pad's box 0.05 (as a pad's size), the layer equal.

## Run it

From this folder:

```sh
netsmith board build    # the schematic, in out/ (no KiCad needed)
netsmith board fab --locked --allow-drc-violations   # the package for the board house, in fab/Rp2350Minimal/; about 3 minutes (the flag: see The reproduction)
```

`--locked` stops the run if the parts it picks differ from `src/main.lock.toml` and never
writes the pick lock; it also means `--pins locked`, which is all there is to say about pins
here, because the board has no pin requests (see The board). With KiCad hidden (`NETSMITH_NO_KICAD=1`)
the run is the same. Then the parity check, from the repository's root, and the overlay it
writes:

```sh
cd examples/rp2350_minimal
netsmith dev parity fab/Rp2350Minimal/Rp2350Minimal.kicad_pcb \
    --svg reference/parity-overlay.svg
```

`reference/parity-overlay.svg` is the picture of the last such run, and the test above checks
that it is current (`fab` is deterministic, so the file only changes when the board does).

`netsmith board compare` takes their board file as one side and the source as the other:

```sh
netsmith board compare reference/RPI-RP2350A-MINIMAL_R4-S1.kicad_pcb src/main.nsm --loose-values
```

and answers `different` with 82 differences, all of one kind: 43 components of theirs with no
counterpart and 39 of the board's with none, because `compare` pairs components by value and
footprint, and their footprints are named `RPI_COMPILED:generic_capc1005x50`,
`RPI_COMPILED:amphenol_10103594-0001lf` and so on where the board's are
`Capacitor_SMD:C_0402_1005Metric`. Their names are not ours to copy (the
footprints of this port are netsmith's own), so the proof of the nets is a test that compares
the wiring alone (next section).

## The physical file

`src/main.physical.nsm` is `physical for Rp2350Minimal`: every figure is read from their board
file (`reference/placements.toml`), in millimetres from the upper-left corner of the outline,
y down, and the comment above each line says which of theirs it is.

- **The outline**: a 52 x 51 mm `Outline` with a 3 mm corner radius.
- **The mounting holes**: four `MountingHole { .package &= "M2.5" }` at their places. The
  standard rows have only M2 (2.2 mm) and M3 (3.2 mm), and theirs are non-plated 2.75 mm, so
  `kicad.toml` has a row for the package `M2.5` and the footprint is a file of the project's own
  library, theirs (`libs/rp2350_original.pretty/none_mh_npth_fd2p75mm_sm3p15mm_ko6mm.kicad_mod`).
- **J1 to J4, SW1 and SW2**: `.place.x`, `.y`, `.rotation` and `.side` of `.usb`, `.header_low`,
  `.header_high`, `.debug`, `.bootsel` and `.reset`. A requirement is measured from the **body**
  of a part (the `F.Fab` outline, else the courtyard), and the checker compares the footprint's
  **origin**, so where the body is not centred on the origin the line states the body's centre:
  J1's courtyard is not centred (its centre is 1.33 mm from the origin) and J4's is 2.7 mm from
  it. A requirement with a single value for every field fixes the part, so these six are put
  exactly where theirs are, and the checker's offsets are 0.000.
- **Everything else** has no line: the MCU, flash, crystal, regulator, inductor, resistors and
  capacitors are the placer's.

Two more files were needed to make the board route, and neither states a requirement:

- **A ground pour** on the back, `.bottom.net &= "GND"` in the board's `.process` in
  `src/main.nsm`. Their board has a ground zone on `B.Cu` too. The pour carries ground: the
  router has no ground to draw on the front, and routes the 179 connections left. With no pour
  the router left 2 of 179 connections unrouted after 223 s (four tries).
- **A placer seed**, `seed = 4` in `src/main.pcb.toml` (the layout file, which keeps a solution
  and never a requirement; it locks no part). With Raspberry Pi's footprints, seeds 0 and 4 route
  completely (220 s and 176 s) and seeds 1, 2 and 3 leave three, two and one connection after
  300 s (the file says why the seed moved). The seed does not move the six parts above, only the
  others.

## The case

`case/` holds a simple two-part case of our own (MIT, `case/LICENSE`; not Raspberry Pi's), so
the example shows the case fit check (ADR 0109). `case/make_case.py` writes both STEP files
(Python 3's standard library only, the same bytes on every run): change a figure there and run
it again. Every solid is a box. The physical file names the two files as `CaseModel`s, `.base`
and `.lid`, placed at x and y -2.5 mm, and z -7.6 mm and 6.5 mm.

- **The base**: a tray with a 2 mm floor and 2 mm walls 0.5 mm off the outline, and four 6 mm
  square bosses, 4 mm tall with a 2.2 mm bore for an M2.5 thread-forming screw, under the
  mounting holes. The board's bottom face rests on them: 4 mm leaves the headers' tails (0.94 mm
  out of the bottom face, F-226's -07 tail of 2.54 mm through the 1.6 mm board, stated as their
  `.pin_protrusion`) 3.06 mm over the floor, and the case fit finds nothing on them. The top wall has a notch at J1, 15 mm wide
  and from 3.4 mm under the board's top face up, for a micro-B plug's overmould; the bottom wall
  has one at J4 for its cable.
- **The lid**: a 2 mm plate whose underside is 6.5 mm above the board's top face, which keeps it
  clear of J1 (2.99 mm) and the plug's overmould. J2 and J3 (8.38 mm) stand through slots 1 mm
  round their bodies, and a 2 mm hole over SW1 and SW2 lets a pin press them.

`netsmith dev board3d --format json` (`case_findings`) and `fab` find no `case_collision`. The parts whose
catalog rows have no height yet are `case_unchecked` warnings under the lid, until their heights
are filled in. With those heights, J2 and J3 get a `case_reach` warning: the check measures a
connector at the board's edge as one plugged in from the side, and these two are plugged in
from above, through the lid's slots. `netsmith view 3d --highlight case:lid` and
`--section y=25.5 --view front` draw the fit.

## The result

The last run (`board fab --locked`, seed 3) on the machine that wrote this (a debug build, in which
`netsmith-pcb` is optimised; one run at a time):

| Step | Result |
|---|---|
| Placement | 43 parts on 52 x 51 mm in 2.6 s |
| Routing | all 179 connections routed, on try 1 of 4, in 34 s (35 s in two earlier runs) |
| Design rules check | passed (0 violations; 6 silkscreen warnings: the texts of J1, J3, H1 and H2 touch the board edge, and two silk lines are 0.09 mm apart) |
| Requirements | 32 of 32 satisfied |
| `fab` in all | 37 s |
| Left to look at | 2 vias stand in pads (C16.1, U1.61): order them as epoxy filled and capped, or `fab-notes.txt` says what else |

What stops a run that does not finish: the router's own limit of 300 s (`--route-timeout`), or
its four tries; it then writes the board marked INCOMPLETE and the run fails (`INCOMPLETE:`, with
the unrouted connections in `routing-failure.txt`). The board is not ready to order then.

The parity checker on that board (`must-match: 225 ok, 0 failed`, which the gate's `min_ok` holds):

| Must match | Result |
|---|---|
| Outline, 52 x 51 mm and radius 3 mm | ok (0.000 off) |
| Mounting holes MH1 to MH4, place, drill 2.75 mm, non-plated, 3.15 mm pad, no net | ok (0.000 off) |
| J1, micro-USB: place, rotation 180, layer, 15 pads | ok |
| J2, 2 x 18 header: place, rotation 270, layer, 36 pads | ok |
| J3, 2 x 18 header: place, rotation 270, layer, 36 pads | ok |
| J4, JST-SH: place, rotation 0, layer, 5 pads | ok |
| SW1, SW2: place, rotation 270 and 180, layer, 4 pads each | ok |
| The pin-to-signal map of J2 and J3 | ok: each header pad is on the pad of U1 that theirs is (the nets are named differently, so the connectivity vouches: 43 warnings say so) |

**What is not matched** (reported, never a failure): the other parts' places and rotations
(U1 is 9.3 mm right and 4.95 mm up from theirs, U2 23.3 mm left and 3.6 mm down, U3 11.1 mm
right and 0.6 mm up, X1 0.75 mm right and 6.1 mm up, L1 9.9 mm right and 10.85 mm up and turned;
the resistors and capacitors are all elsewhere), the pads of those parts where netsmith's
footprint is not theirs (U1: 61 pads differ in centre, size or drill, and 18 of theirs have no
partner), and the routing: the copper is netsmith's own, and nothing is claimed about it. 82 items are `info`.
`reference/parity-overlay.svg` draws both boards at one scale (theirs blue, netsmith's orange,
a failing must-match item red): the outline, the holes, the four edge connectors and the two
buttons coincide, and the chip, the flash, the regulator and the rest are where the placer
put them. Open it in a browser.

## The reproduction

Beside the board that `netsmith board fab` makes of this project (the automatic board, placed and
routed by netsmith), the port keeps a reproduction of Raspberry Pi's own copper (issue #599; the
language guide's "Reproducing a KiCad board"): `reference/agent/main.routes.toml` and
`reference/agent/main.pcb.toml`, which `netsmith routes import reference/RPI-RP2350A-MINIMAL_R4-S1.kicad_pcb` writes.
They are kept out of `src/`, so `fab` here still makes the automatic board; `scripts/reproductions
--update` writes them again when a footprint, the placer or the importer changes. The test
`reproduce::the_rp2350_reproduction_has_the_originals_copper` (`crates/netsmith-cli/tests/reproduce.rs`) imports again and requires the
committed files, puts them into `src/` of a copy, runs `fab` with no KiCad and compares the copper
of the board it writes with Raspberry Pi's, shape by shape, as sets, to 0.1 µm: every segment, arc and
via on its layer and net, and every zone on its layers with its outline, holes and settings
(issue #724).

| Copper | Segments | Arcs | Vias | Track length |
|---|---|---|---|---|
| Automatic board | 1351 | 387 | 182 | 2012.5 mm |
| Reproduction | 352 | 0 | 40 | 1086.0 mm |
| Raspberry Pi's | 352 | 0 | 40 | 1086.0 mm |

The automatic board's figures are of 2026-11-14 and change with the placer and the router;
`cargo test -p netsmith-cli --test main reproduce::measured -- --ignored --nocapture` prints all
three again, with what netsmith's design rules check finds on the reproduction.

**What matches:** all 352 segments and 40 vias of Raspberry Pi's board, each on its layer and
net, and nothing more, and all 10 of its zones (VBUS, +3V3, +1V1, GND and VREG_LX on F.Cu, nine
of them, and GND on B.Cu), each on its layer and net with its outline, holes, priority and
settings: the routes file holds them, and the board file `fab` writes holds them as KiCad's zones,
in place of the design's ground pour on B.Cu. The zones join their nets as their fill reaches, so
the router draws nothing: VREG_LX, which their board joins by a zone alone, gets no track. Every
part is drawn with their footprint (see Parts), so the nine plated holes of the RP2350's exposed
pad join it to the ground zone on B.Cu and `fab` leaves no connection; the import places every
part where their board has it, as their board turns it, locked (the physical file pins the
connectors and buttons at the same places). The test compares each footprint of the
reproduction with theirs (`netsmith_tools::footprint_diff`: place, turn, face, every pad's
number, centre, size, shape, drill, layers and net, and the courtyard, to 5 µm): all 47 parts are
theirs but U2, whose tab is numbered 2 where theirs is numbered 4 (see Parts). No two courtyards
overlap, and netsmith's design rules check finds no short, no clearance and no overlap.

**What does not, and why:**

- **The fill.** `fab`'s Gerbers hold netsmith's fill of the zones, which keeps every clearance
  but removes no island and trims no sliver narrower than a zone's minimum width; KiCad's fill of
  the board file (the zones are written unfilled) removes them, as their board's does.
- **U2's tab** is numbered 2, not 4 (see Parts): the same copper on the same net.
- **What their board breaks of JLCPCB's rules.** `fab`'s design rules check (with the process's
  rules) finds one thing on the reproduction, on their board too, which the test measures by
  running the check on their file: three bends of their +3V3 tracks are sharper than the 45
  degrees netsmith allows (`track_angle`, 3). The board is packaged with
  `--allow-drc-violations` and `fab-notes.txt` lists them. The nine vias in the RP2350's exposed
  pad are 0.6 mm pads round 0.25 mm holes, a ring of 0.175 mm alone where JLCPCB asks 0.18 mm,
  but each is measured with the exposed pad of its number that it touches, as KiCad measures it
  (issue #1185), so neither board has a `plated_ring` finding.

Netsmith's design rules check finds nothing else: no short, no clearance and no courtyard
overlap.

## The board

`src/main.nsm` is the circuit of Raspberry Pi's board in netsmith's words, not a netlist:

- **Rails.** `.vbus` (the USB supply), `.v3v3` (the regulator's output) and `.v1v1` (the core
  supply, made by the chip's own switching regulator with L1: there is no std part for a
  regulator inside a chip, so it is a rail the board joins to the pins and the inductor), with
  the nets named `VBUS`, `+3V3`, `+1V1` and `GND` as theirs are. The regulator is the standard
  `LinearRegulator` asked for the SOT-223 row of `catalogs/ldo.csv`.
- **Modules.** `Oscillator` (`src/oscillator.nsm`): the crystal, its two 15 pF load capacitors
  and the 1 kohm damping resistor, joined to the chip by `.xin`, `.xout` and `.gnd`.
- **Generics with their values.** Every resistor and capacitor is a `Resistor` or `Capacitor`
  with Raspberry Pi's value and tolerance and the package of their footprint (`1005` metric is
  `0402`, `2012` is `0805`; the tolerances are the 1 % of the resistors, 10 % of the 100 nF and
  10 uF, 20 % of the 4.7 uF and 5 % of the 15 pF, from the Description property of each part).
  R1 is a `PullUp` whose resistor's package the board narrows (`.resistor.package &= "0402"`). The 1 kohm in
  front of each button is a plain `Resistor`.
- **The headers' pin map is fixed.** `.header_low` (J2) and `.header_high` (J3) are joined
  pin by pin to **named** pins of the chip (`.header_low.p12 ~ .mcu.gpio4`), exactly as their
  pads are. The pin optimizer of `fab` (ADR 0101) moves only a pin that a *request* got
  (`.x: .mcu.GPIO`), never a pin the source names, and this board has no request, so no
  `main.pins.toml` and nothing to move. A test holds it: the optimizer's input is empty here, and
  the same board with one header pad joined to a request is one it could move.
- **The parts** are theirs: 39 of their 43 footprints; the other four are the mounting holes,
  which belong to the physical file.

### Same nets

`cargo test -p netsmith-tools --test main rp2350_minimal::board::` runs these (none needs KiCad):

- `every_pad_has_the_same_pads_on_its_net_as_in_raspberry_pis_board`: reads the committed
  `.kicad_pcb` as a file (`Netlist::from_kicad_pcb`, netsmith's own s-expression reader, the one
  `compare` uses) and the design's nets, pairs the parts by the table in the test (the path of
  each member and Raspberry Pi's designator), and fails when **any pad of any of the 39 parts has
  a different set of other pads on its net**. Netsmith's net names differ and do not matter.
- `netsmith_compare_says_the_nets_are_the_same`: the same two netlists with value and
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
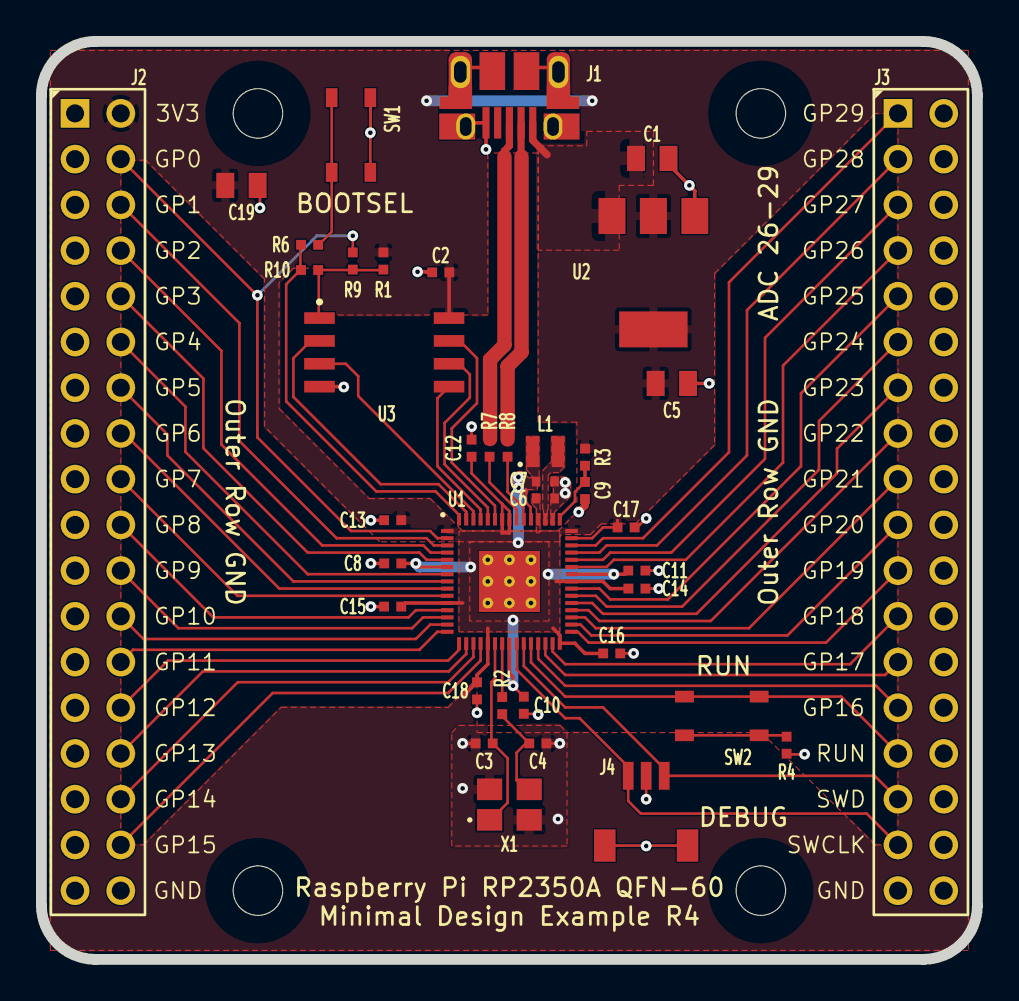
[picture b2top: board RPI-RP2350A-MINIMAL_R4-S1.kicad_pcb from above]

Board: 2 copper layers, 52.0 x 51.0 mm, 43 parts (0 on the bottom side), 55 nets.

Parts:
C1, C5, C19: 10u; generic_capc2012x125
C2, C8, C10, C11, C12, C13, C14, C15, C16, C17, C18: 100n; generic_capc1005x50
C3, C4: 15p; generic_capc1005x50
C6, C7: 4.7u; generic_capc1005x50_wide
C9: 4.7u; generic_capc1005x50
J1: 10103594-0001LF; amphenol_10103594-0001lf
J2, J3: TSW-118-07-L-D; samtec_tsw-118-07-l-d
J4: SM03B-SRSS-TB(LF)(SN); jst_sm03b-srss-tb-lf--sn-
L1: 3.3u; abracon_aota-b201610s3r3-101-t
MH1, MH2, MH3, MH4: NPTH FD2.75mm SM3.15mm KO6mm; none_mh_npth_fd2p75mm_sm3p15mm_ko6mm
R1: 10k; generic_resc1005x35
R2, R4, R6: 1k; generic_resc1005x35
R3: 33; generic_resc1005x35
R7, R8: 27; generic_resc1005x35
R9, R10: 0; generic_resc1005x35
SW1, SW2: 434133025816; wurthelek_434133025816
U1: RP2350A; rpi_rp2350a_vias
U2: NCP1117ST33T3G; onsemi_ncp1117st33t3g
U3: W25Q128JVSIQ; generic_soic127p790x195-8
X1: 12MHz; generic_xtalcc320x250x80-4

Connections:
+1V1: C7.1, C8.1, C10.1, C11.1, L1.1, U1.6 (DVDD), U1.23 (DVDD), U1.39 (DVDD), U1.50 (VREG_FB)
+3V3: C2.1, C5.1, C6.1, C12.1, C13.1, C14.1, C15.1, C16.1, C17.1, C18.1, C19.1, J2.2, R1.1, R3.1, U1.1 (IOVDD), U1.11 (IOVDD), U1.20 (IOVDD), U1.30 (IOVDD), U1.38 (IOVDD), U1.44 (ADC_AVDD), U1.45 (IOVDD), U1.49 (VREG_VIN), U1.53 (USB_OTP_VDD), U1.54 (QSPI_IOVDD), U2.2 (OUT), U2.4 (OUT), U3.8 (VCC)
/FLASH_SS: R1.2, R9.2, R10.2, U3.1 (~CS)
/GPIO0: J2.4, R9.1, U1.2 (GPIO0)
/GPIO1: J2.6, U1.3 (GPIO1)
/GPIO2: J2.8, U1.4 (GPIO2)
/GPIO3: J2.10, U1.5 (GPIO3)
/GPIO4: J2.12, U1.7 (GPIO4)
/GPIO5: J2.14, U1.8 (GPIO5)
/GPIO6: J2.16, U1.9 (GPIO6)
/GPIO7: J2.18, U1.10 (GPIO7)
/GPIO8: J2.20, U1.12 (GPIO8)
/GPIO9: J2.22, U1.13 (GPIO9)
/GPIO10: J2.24, U1.14 (GPIO10)
/GPIO11: J2.26, U1.15 (GPIO11)
/GPIO12: J2.28, U1.16 (GPIO12)
/GPIO13: J2.30, U1.17 (GPIO13)
/GPIO14: J2.32, U1.18 (GPIO14)
/GPIO15: J2.34, U1.19 (GPIO15)
/GPIO16: J3.27, U1.27 (GPIO16)
/GPIO17: J3.25, U1.28 (GPIO17)
/GPIO18: J3.23, U1.29 (GPIO18)
/GPIO19: J3.21, U1.31 (GPIO19)
/GPIO20: J3.19, U1.32 (GPIO20)
/GPIO21: J3.17, U1.33 (GPIO21)
/GPIO22: J3.15, U1.34 (GPIO22)
/GPIO23: J3.13, U1.35 (GPIO23)
/GPIO24: J3.11, U1.36 (GPIO24)
/GPIO25: J3.9, U1.37 (GPIO25)
/GPIO26_ADC0: J3.7, U1.40 (GPIO26_ADC0)
/GPIO27_ADC1: J3.5, U1.41 (GPIO27_ADC1)
/GPIO28_ADC2: J3.3, U1.42 (GPIO28_ADC2)
/GPIO29_ADC3: J3.1, U1.43 (GPIO29_ADC3)
/QSPI_SCLK: U1.56 (QSPI_SCLK), U3.6 (CLK)
/QSPI_SD0: U1.57 (QSPI_SD0), U3.5 (DI_IO0)
/QSPI_SD1: U1.59 (QSPI_SD1), U3.2 (DO_IO1)
/QSPI_SD2: U1.58 (QSPI_SD2), U3.3 (~WP_IO2)
/QSPI_SD3: U1.55 (QSPI_SD3), U3.7 (~HOLD_IO3)
/QSPI_SS: R6.1, R10.1, U1.60 (QSPI_~SS)
/RUN: J3.29, SW2.3, SW2.4, U1.26 (RUN)
/SWCLK: J3.33, J4.1, U1.24 (SWCLK)
/SWD: J3.31, J4.3, U1.25 (SWDIO)
/USB_D+: J1.3 (D+), R7.1
/USB_D-: J1.2 (D-), R8.1
/VREG_AVDD: C9.1, R3.2, U1.46 (VREG_AVDD)
/VREG_LX: L1.2, U1.48 (VREG_LX)
/XIN: C3.1, U1.21 (XIN), X1.1
/XOUT: R2.1, U1.22 (XOUT)
/~USB_BOOT: R6.2, SW1.3, SW1.4
GND: C1.2, C2.2, C3.2, C4.2, C5.2, C6.2, C7.2, C8.2, C9.2, C10.2, C11.2, C12.2, C13.2, C14.2, C15.2, C16.2, C17.2, C18.2, C19.2, J1.5 (GND), J1.6 (SH), J1.7 (SH), J1.8 (SH), J1.9 (SH), J1.10 (SH), J1.11 (SH), J2.1, J2.3, J2.5, J2.7, J2.9, J2.11, J2.13, J2.15, J2.17, J2.19, J2.21, J2.23, J2.25, J2.27, J2.29, J2.31, J2.33, J2.35, J2.36, J3.2, J3.4, J3.6, J3.8, J3.10, J3.12, J3.14, J3.16, J3.18, J3.20, J3.22, J3.24, J3.26, J3.28, J3.30, J3.32, J3.34, J3.35, J3.36, J4.2, J4.4 (SH1), J4.5 (SH2), R4.2, SW1.1, SW1.2, U1.47 (VREG_PGND), U1.61 (GND), U2.1 (GND), U3.4 (GND), X1.2, X1.4
unnamed: C4.1, R2.2, X1.3
unnamed: R4.1, SW2.1, SW2.2
unnamed: R8.2, U1.51 (USB_DM)
unnamed: R7.2, U1.52 (USB_DP)
VBUS: C1.1, J1.1 (VCC), U2.3 (IN)

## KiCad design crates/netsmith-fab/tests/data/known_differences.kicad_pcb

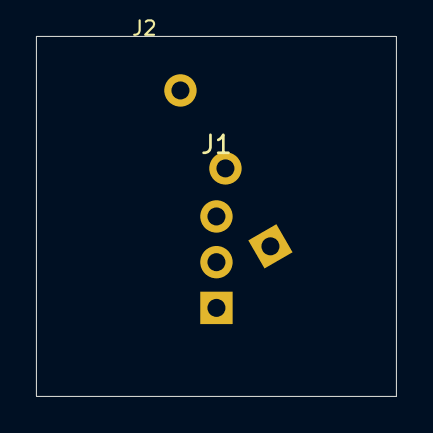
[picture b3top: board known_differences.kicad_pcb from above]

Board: 4 copper layers, 20.0 x 20.0 mm, 3 parts (1 on the bottom side), 2 nets, no tracks yet.

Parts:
J1: hdr; Header
J2: round; Round
R1: 1k; Back

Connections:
GND: J1.1, J1.3, J2.1, J2.2, J2.3
SIG: J1.2, R1.1, R1.2
